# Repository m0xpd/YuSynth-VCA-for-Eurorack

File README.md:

# YuSynth-VCA-for-Eurorack

**A Eurorack Version of Yves Usson's 'Simple VCA'**

This repository contains design files for my Eurorack version of Yves Usson's 'Simple VCA' circuit:
http://yusynth.net/Modular/EN/VCA/index.html

which has been described in a stripboard implemementation on Eddy Bergman's Synth DIY site:
https://www.eddybergman.com/2020/04/synthesizer-build-part-29-vca-yusynth_25.html

**Circuit Description**

This Eurorack version is implemented on a single PCB, following closely Yves' original schematic.<p>(You can see my schematic as a graphic [here](https://github.com/m0xpd/YuSynth-VCA-for-Eurorack/blob/main/PCB/YuSynth%20Eurorack%20VCA%20Schematic.png) and the BoM is [here](https://github.com/m0xpd/YuSynth-VCA-for-Eurorack/blob/main/PCB/YuSynth%20VCA%20Eurorack%20v1%20BOM.txt) )

I have replaced the specified BC547 transistors with 2n3904s, as these are my everyday 'popcorn' NPNs. Yves does note this as a standard replacement 
and warns that the pinouts of the two transistors is revesed; 'CBE' becomes 'EBC'. 

My PCB is designed and silkscreened for 2n3904s, so if you want to swap back to the original BC547Cs, you'll have to place these 'in reverse' 
(i.e. with the flat face of the case aligned with the curve on the silkscreen).

I have also swapped the two IC packages (a TL072 and a LM741/TL071) for a single TL074 for two reasons:
Firstly, it is more efficient in terms of PCB area to do this.
Secondly, it is cheaper to do this; TL074s are more efficient than their smaller siblings (they only need one pair of power supply pins) but they're 
also very widely used so they are cheap, whereas TL072s and (particularly) TL071s are disproportionately expensive. Even more perversely, the old LM 
or uA741 (which was once the only op-amp in the shop) is now available only as a nostalgia piece, so it too sells for crazy money!

Having done this, I couldn't bear to have that extra op-amp stage doing nothing, so I gave both outputs independent active drive.

**Licensing the IP**

[![CC BY-NC-SA 4.0][cc-by-nc-sa-image]][cc-by-nc-sa]

[cc-by-nc-sa]: http://creativecommons.org/licenses/by-nc-sa/4.0/
[cc-by-nc-sa-image]: https://licensebuttons.net/l/by-nc-sa/4.0/88x31.png
[cc-by-nc-sa-shield]: https://img.shields.io/badge/License-CC%20BY--NC--SA%204.0-lightgrey.svg  
  
Yves is clear on the position with copyright on his website:

"All circuits, schematics, printed circuit board, panel design and associated data published on (yusynth.net) can be used for private use only." 

and:

"The projects of (yusynth.net) may be build for personal, private usage or educative purpose. Commercial exploitation of the schematics, circuits, 
front panels and software shown on (yusynth.net), is not permitted without a formal agreement with (Yves Usson)".

Accordingly, **the copyright for this VCA circuit rests with Yves and no commercial exploitation is permitted**.

I have reflected this in the [License](LICENSE.txt) for the Eurorack version presented in this repository.

This work is licensed under a
[Creative Commons Attribution-NonCommercial-ShareAlike 4.0 International License.](https://creativecommons.org/licenses/by-nc-sa/4.0/deed.en)

**Hardware Design Files: PCB**

The PCB is described by .sch and .brd files and a BoM located in the [PCB folder](https://github.com/m0xpd/YuSynth-VCA-for-Eurorack/tree/main/PCB). 

**Hardware Design Files : Front Panel**

A front panel to complete the module is described by a simple Kicad project located in the [Front_Panel folder](https://github.com/m0xpd/YuSynth-VCA-for-Eurorack/tree/main/Front_Panel). 

**SetUp / Calibration**

Yves offers a [useful description of setup](http://yusynth.net/Modular/EN/VCA/index.html), which assumes the availability of an oscilloscope. 
I imagine the circuit could be setup adequately without a 'scope - but I've never tried to do it! Certainly an a.c. coupled build of this VCA
could be made to work adequately without access to a 'scope in the setup phase, but I think it would be tricky to setup a d.c. coupled version without access 
to appropriate test gear.

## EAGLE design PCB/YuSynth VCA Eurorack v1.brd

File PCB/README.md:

[This folder](https://github.com/m0xpd/YuSynth-VCA-for-Eurorack/tree/main/PCB) contains design files for the Eurocard version of the YuSynth VCA printed circuit board developed in AutoCAD EAGLE.

These can be loaded into the (free) version of Eagle:
https://www.autodesk.co.uk/products/eagle/features
and are ready for the CAM processor to produce Gerber files ready to send to a PCB house. 

I have used JLCPCB (https://jlcpcb.com/) to produce the prototype seen in the pictures below (usual disclaimer). 
JLCPCB offer a file to set up the CAM processor to produce the Gerbers in the correct format - it is available (along with some guidelines) here:
https://support.jlcpcb.com/article/137-how-to-generate-gerber-and-drill-files-in-autodesk-eagle

I'm sure the other PCB houses offer an equivalent service - but I can't speak from first-hand experience.

The unpopulated board is seen here:

and the populated board is seen here (both from the 'front side', usually obscured by the front panel and from the back):

**Bill of Materials**

The [BoM](https://github.com/m0xpd/YuSynth-VCA-for-Eurorack/blob/main/PCB/YuSynth%20VCA%20Eurorack%20v1%20BOM.txt) is presented in the rather verbose format produced by Eagle; some additional notes might be useful.

Firstly, Yves explains that two versions of the VCA can be constructed: an a.c. coupled version (for handling 'audio' signals) and a d.c. version 
(useful for controlling CV signals).

The a.c. coupled version is the standard build. It uses all the parts in the BoM. The three 100k control potentiometers should be logarithmic 
taper types in this application, 'A100K'. Linear taper potentiometers will work, but they will give the usual poor mapping between rotational angle 
and 'loudness'. Note that these potentiometers are named in my schematic with idents 'SIGLEVEL', 'GAIN', and 'CTLLEVEL' (Yves uses the idents 'P1', 'P2' 
and 'P3').

The d.c. coupled version is non-standard. To make the system d.c. coupled, capacitors C3 and C4 must be replaced by wire links. Also, the signal 
level monitor will not operate as intended and should be omitted (do not fit R24 & 25, C8 & 9 D1, LED1 and T4). In this case, the three control
potentiometers should be linear taper, 'B100K'.

I've made both versions.

Some components are mechanically critical in my design; the control potentiometers are 9mm vertical Alpha types such as [this](https://www.thonk.co.uk/shop/alpha-9mm-pots-vertical-t18/) and the jacks are [Thonkiconns](https://www.thonk.co.uk/shop/thonkiconn/).

Back in the day I used 3-way Molex KK connectors for powering modules and I still fit these as an alternative to the standard Eurorack power 
connector if space is available - you can omit the three way 'POWER' header if you don't plan to use it!

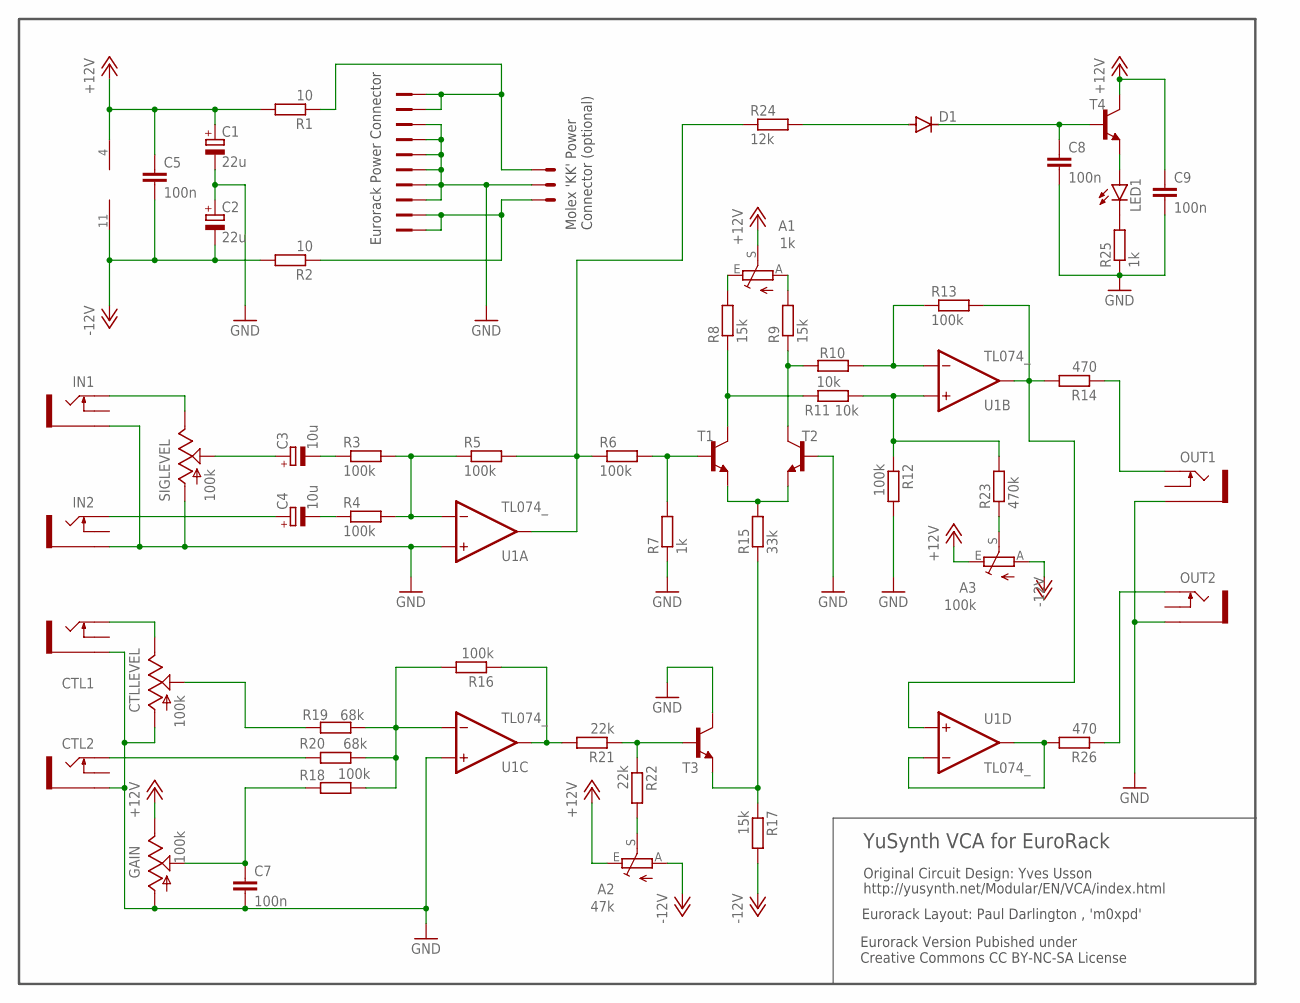
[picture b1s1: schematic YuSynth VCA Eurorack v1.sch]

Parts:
A1: 1k; B25P
A2: 47k; B25P
A3: 100k; B25P
C1, C2: 22u; E2,5-5
C3, C4: 10u; E2,5-5
C5, C7, C8, C9: 100n; C050-025X075
CTL1, CTL2: THONKICONNNEW; WQP-PJ301M-12_JACK
CTLLEVEL: 100k; 9MM_SNAP-IN_POT
D1: 1N4148DO35-7; DO35-7
EURORACK_POWER: 2510-; PAK100/2500-10
GAIN: 100k; 9MM_SNAP-IN_POT
IN1, IN2: THONKICONNNEW; WQP-PJ301M-12_JACK
LED1: LED3MM
OUT1, OUT2: THONKICONNNEW; WQP-PJ301M-12_JACK
POWER: 22-23-2031
R1, R2: 10; 0204/7
R3, R4, R5, R6, R12, R13, R16, R18: 100k; 0204/7
R7, R25: 1k; 0204/7
R8, R9, R17: 15k; 0204/7
R10, R11: 10k; 0204/7
R14, R26: 470; 0204/7
R15: 33k; 0204/7
R19, R20: 68k; 0204/7
R21, R22: 22k; 0204/7
R23: 470k; 0204/7
R24: 12k; 0204/7
SIGLEVEL: 100k; 9MM_SNAP-IN_POT
T1, T2, T3, T4: 2N3904; TO92
U1: TL074_; DIL14

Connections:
+12V: A1.S, A2.E, A3.E, C1.+, C5.1, C9.1, GAIN.3 (E), R1.2, T4.1 (C), U1.4 (V+)
-12V: A2.A, A3.A, C2.-, C5.2, R2.2, R17.2, U1.11 (V-)
GND: C1.-, C2.+, C7.2, C8.2, C9.2, CTL1.P$3_SLEEVE (SLEEVE), CTL2.P$3_SLEEVE (SLEEVE), CTLLEVEL.1 (A), EURORACK_POWER.3, EURORACK_POWER.4, EURORACK_POWER.5, EURORACK_POWER.6, EURORACK_POWER.7, EURORACK_POWER.8, GAIN.1 (A), IN1.P$3_SLEEVE (SLEEVE), IN2.P$3_SLEEVE (SLEEVE), OUT1.P$3_SLEEVE (SLEEVE), OUT2.P$3_SLEEVE (SLEEVE), POWER.2, R7.1, R12.2, R25.1, SIGLEVEL.1 (A), T2.2 (B), T3.1 (C), U1.3 (+IN), U1.10 (+IN)
unnamed: IN1.P$1_TIP (TIP), SIGLEVEL.3 (E)
unnamed: LED1.K (C), R25.2
unnamed: C3.+, SIGLEVEL.2 (S)
unnamed: C3.-, R3.1
unnamed: C4.+, IN2.P$1_TIP (TIP)
unnamed: C4.-, R4.1
unnamed: R3.2, R4.2, R5.1, U1.2 (-IN)
unnamed: R16.2, R18.1, R19.1, R20.1, U1.9 (-IN)
unnamed: R15.1, R17.1, T3.3 (E)
unnamed: CTL2.P$1_TIP (TIP), R20.2
unnamed: CTL1.P$1_TIP (TIP), CTLLEVEL.3 (E)
unnamed: R6.2, R7.2, T1.2 (B)
unnamed: R16.1, R21.2, U1.8 (OUT)
unnamed: R21.1, R22.1, T3.2 (B)
unnamed: A2.S, R22.2
unnamed: R8.1, R11.2, T1.1 (C)
unnamed: R9.1, R10.2, T2.1 (C)
unnamed: R15.2, T1.3 (E), T2.3 (E)
unnamed: A1.E, R8.2
unnamed: A1.A, R9.2
unnamed: A3.S, R23.1
unnamed: R10.1, R13.1, U1.6 (-IN)
unnamed: R11.1, R12.1, R23.2, U1.5 (+IN)
unnamed: R13.2, R14.2, U1.7 (OUT), U1.12 (+IN)
unnamed: D1.A, R24.2
unnamed: C8.1, D1.C, T4.2 (B)
unnamed: R26.2, U1.13 (-IN), U1.14 (OUT)
unnamed: OUT1.P$1_TIP (TIP), R14.1
unnamed: LED1.A, T4.3 (E)
unnamed: R5.2, R6.1, R24.1, U1.1 (OUT)
unnamed: OUT2.P$1_TIP (TIP), R26.1
unnamed: CTLLEVEL.2 (S), R19.2
unnamed: C7.1, GAIN.2 (S), R18.2
unnamed: EURORACK_POWER.9, EURORACK_POWER.10, POWER.1, R1.1
unnamed: EURORACK_POWER.1, EURORACK_POWER.2, POWER.3, R2.1

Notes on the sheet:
YuSynth VCA for EuroRack
Original Circuit Design: Yves Usson
Eurorack Layout: Paul Darlington , 'm0xpd'
Eurorack Version Pubished under Creative Commons CC BY-NC-SA License
Eurorack Power Connector
Molex 'KK' Power Connector (optional)
http://yusynth.net/Modular/EN/VCA/index.html

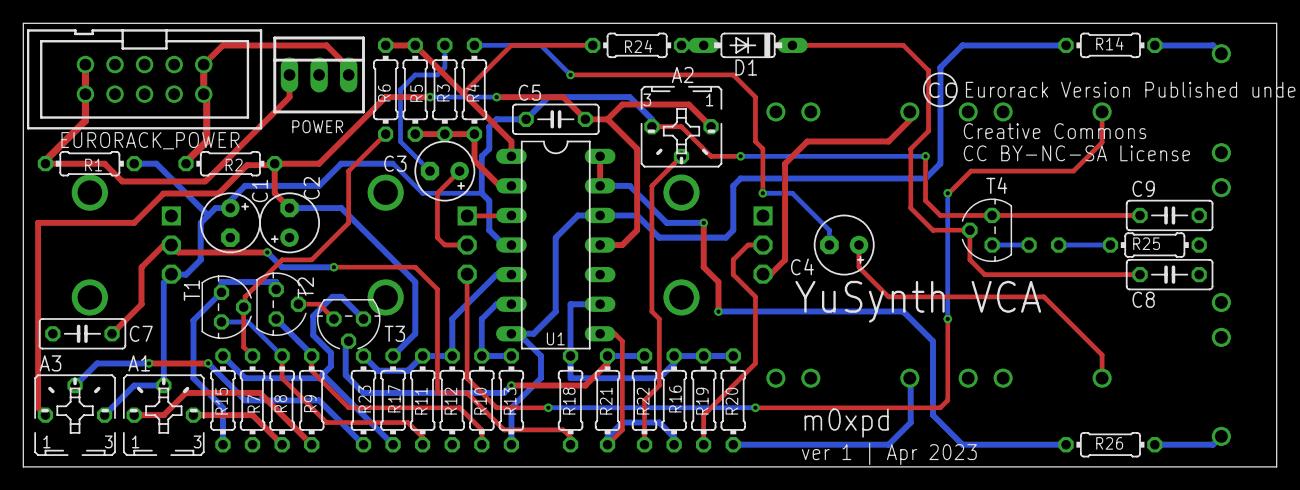
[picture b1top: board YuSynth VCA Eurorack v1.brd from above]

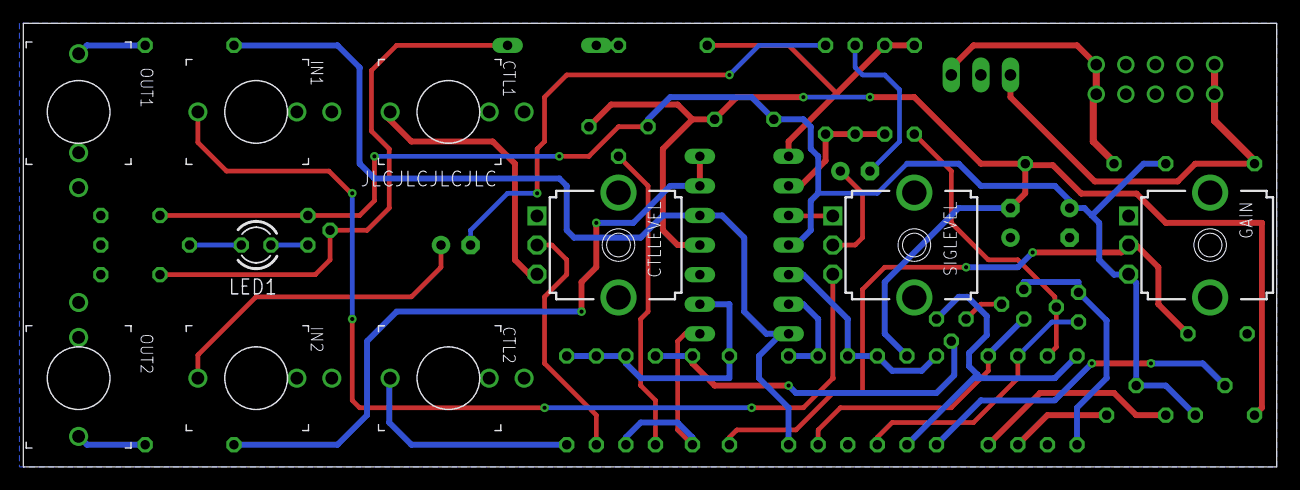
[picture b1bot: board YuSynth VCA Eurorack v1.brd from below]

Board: 2 copper layers, 107.6 x 38.1 mm, 55 parts (10 on the bottom side), 38 nets.

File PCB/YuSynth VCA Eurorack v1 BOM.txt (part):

Partlist exported from /Users/pauldarlington/Documents/EAGLE/projects/YUSynth VCA/YuSynth VCA Eurorack v1.sch at 16/04/2023 07:21

Part           Value         Device           Package            Description                                       MF    MPN         OC_FARNELL OC_NEWARK POPULARITY SPICEPREFIX
A1             1k            TRIM_EU-B25P     B25P               POTENTIOMETER                                                                            7                     
A2             47k           TRIM_EU-B25P     B25P               POTENTIOMETER                                                                            7                     
A3             100k          TRIM_EU-B25P     B25P               POTENTIOMETER                                                                            7                     
C1             22u           CPOL-EUE2.5-5    E2,5-5             POLARIZED CAPACITOR, European symbol                                                     16         C          
C2             22u           CPOL-EUE2.5-5    E2,5-5             POLARIZED CAPACITOR, European symbol                                                     16         C          
C3             10u           CPOL-EUE2.5-5    E2,5-5             POLARIZED CAPACITOR, European symbol                                                     16         C          
C4             10u           CPOL-EUE2.5-5    E2,5-5             POLARIZED CAPACITOR, European symbol                                                     16         C          
C5             100n          C-EU050-025X075  C050-025X075       CAPACITOR, European symbol                                                               29         C          
C7             100n          C-EU050-025X075  C050-025X075       CAPACITOR, European symbol                                                               29         C          
C8             100n          C-EU050-025X075  C050-025X075       CAPACITOR, European symbol                                                               29         C          
C9             100n          C-EU050-025X075  C050-025X075       CAPACITOR, European symbol                                                               29         C          
CTL1           THONKICONNNEW THONKICONNNEW    WQP-PJ301M-12_JACK 3.5mm socket for Eurorack modular synths                                                                       
CTL2           THONKICONNNEW THONKICONNNEW    WQP-PJ301M-12_JACK 3.5mm socket for Eurorack modular synths                                                                       
CTLLEVEL       100k          9MM_SNAP-IN_POT_ 9MM_SNAP-IN_POT    9mm vertical snap-in pot, Alpha / Panasonic style                                                              
D1             1N4148DO35-7  1N4148DO35-7     DO35-7             DIODE                                                                                    58                    
EURORACK_POWER 2510-         2510-            PAK100/2500-10     3M (TM) Pak 100 4-Wall Header                     3M    2510-6002UB 9838244    46F4725   0                     
GAIN           100k          9MM_SNAP-IN_POT_ 9MM_SNAP-IN_POT    9mm vertical snap-in pot, Alpha / Panasonic style                                                              
IN1            THONKICONNNEW THONKICONNNEW    WQP-PJ301M-12_JACK 3.5mm socket for Eurorack modular synths                                                                       
IN2            THONKICONNNEW THONKICONNNEW    WQP-PJ301M-12_JACK 3.5mm socket for Eurorack modular synths                                                                       
LED1                         LED3MM           LED3MM             LED                                                                                      97                    
OUT1           THONKICONNNEW THONKICONNNEW    WQP-PJ301M-12_JACK 3.5mm socket for Eurorack modular synths                                                                       
OUT2           THONKICONNNEW THONKICONNNEW    WQP-PJ301M-12_JACK 3.5mm socket for Eurorack modular synths                                                                       
POWER          22-23-2031    22-23-2031       22-23-2031         .100" (2.54mm) Center Header - 3 Pin              MOLEX 22-23-2031  1462950    30C0862   35                    
R1             10            R-EU_0204/7      0204/7             RESISTOR, European symbol                                                                79         R          
R2             10            R-EU_0204/7      0204/7             RESISTOR, European symbol                                                                79         R          
R3             100k          R-EU_0204/7      0204/7             RESISTOR, European symbol                                                                79         R          
R4             100k          R-EU_0204/7      0204/7             RESISTOR, European symbol                                                                79         R          
R5             100k          R-EU_0204/7      0204/7             RESISTOR, European symbol                                                                79         R          
R6             100k          R-EU_0204/7      0204/7             RESISTOR, European symbol                                                                79         R          
R7             1k            R-EU_0204/7      0204/7             RESISTOR, European symbol                                                                79         R          
R8             15k           R-EU_0204/7      0204/7             RESISTOR, European symbol                                                                79         R          
R9             15k           R-EU_0204/7      0204/7             RESISTOR, European symbol                                                                79         R          
R10            10k           R-EU_0204/7      0204/7             RESISTOR, European symbol                                                                79         R          
R11            10k           R-EU_0204/7      0204/7             RESISTOR, European symbol                                                                79         R          
R12            100k          R-EU_0204/7      0204/7             RESISTOR, European symbol                                                                79         R          
R13            100k          R-EU_0204/7      0204/7             RESISTOR, European symbol                                                                79         R          
R14            470           R-EU_0204/7      0204/7             RESISTOR, European symbol                                                                79         R          
R15            33k           R-EU_0204/7      0204/7             RESISTOR, European symbol                                                                79         R          
R16            100k          R-EU_0204/7      0204/7             RESISTOR, European symbol                                                                79         R          
R17            15k           R-EU_0204/7      0204/7             RESISTOR, European symbol                                                                79         R          
R18            100k          R-EU_0204/7      0204/7             RESISTOR, European symbol                                                                79         R          
R19            68k           R-EU_0204/7      0204/7             RESISTOR, European symbol                                                                79         R          
R20            68k           R-EU_0204/7      0204/7             RESISTOR, European symbol                                                                79         R          
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
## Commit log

2023-04-15 Rename INFO.md to README.md
